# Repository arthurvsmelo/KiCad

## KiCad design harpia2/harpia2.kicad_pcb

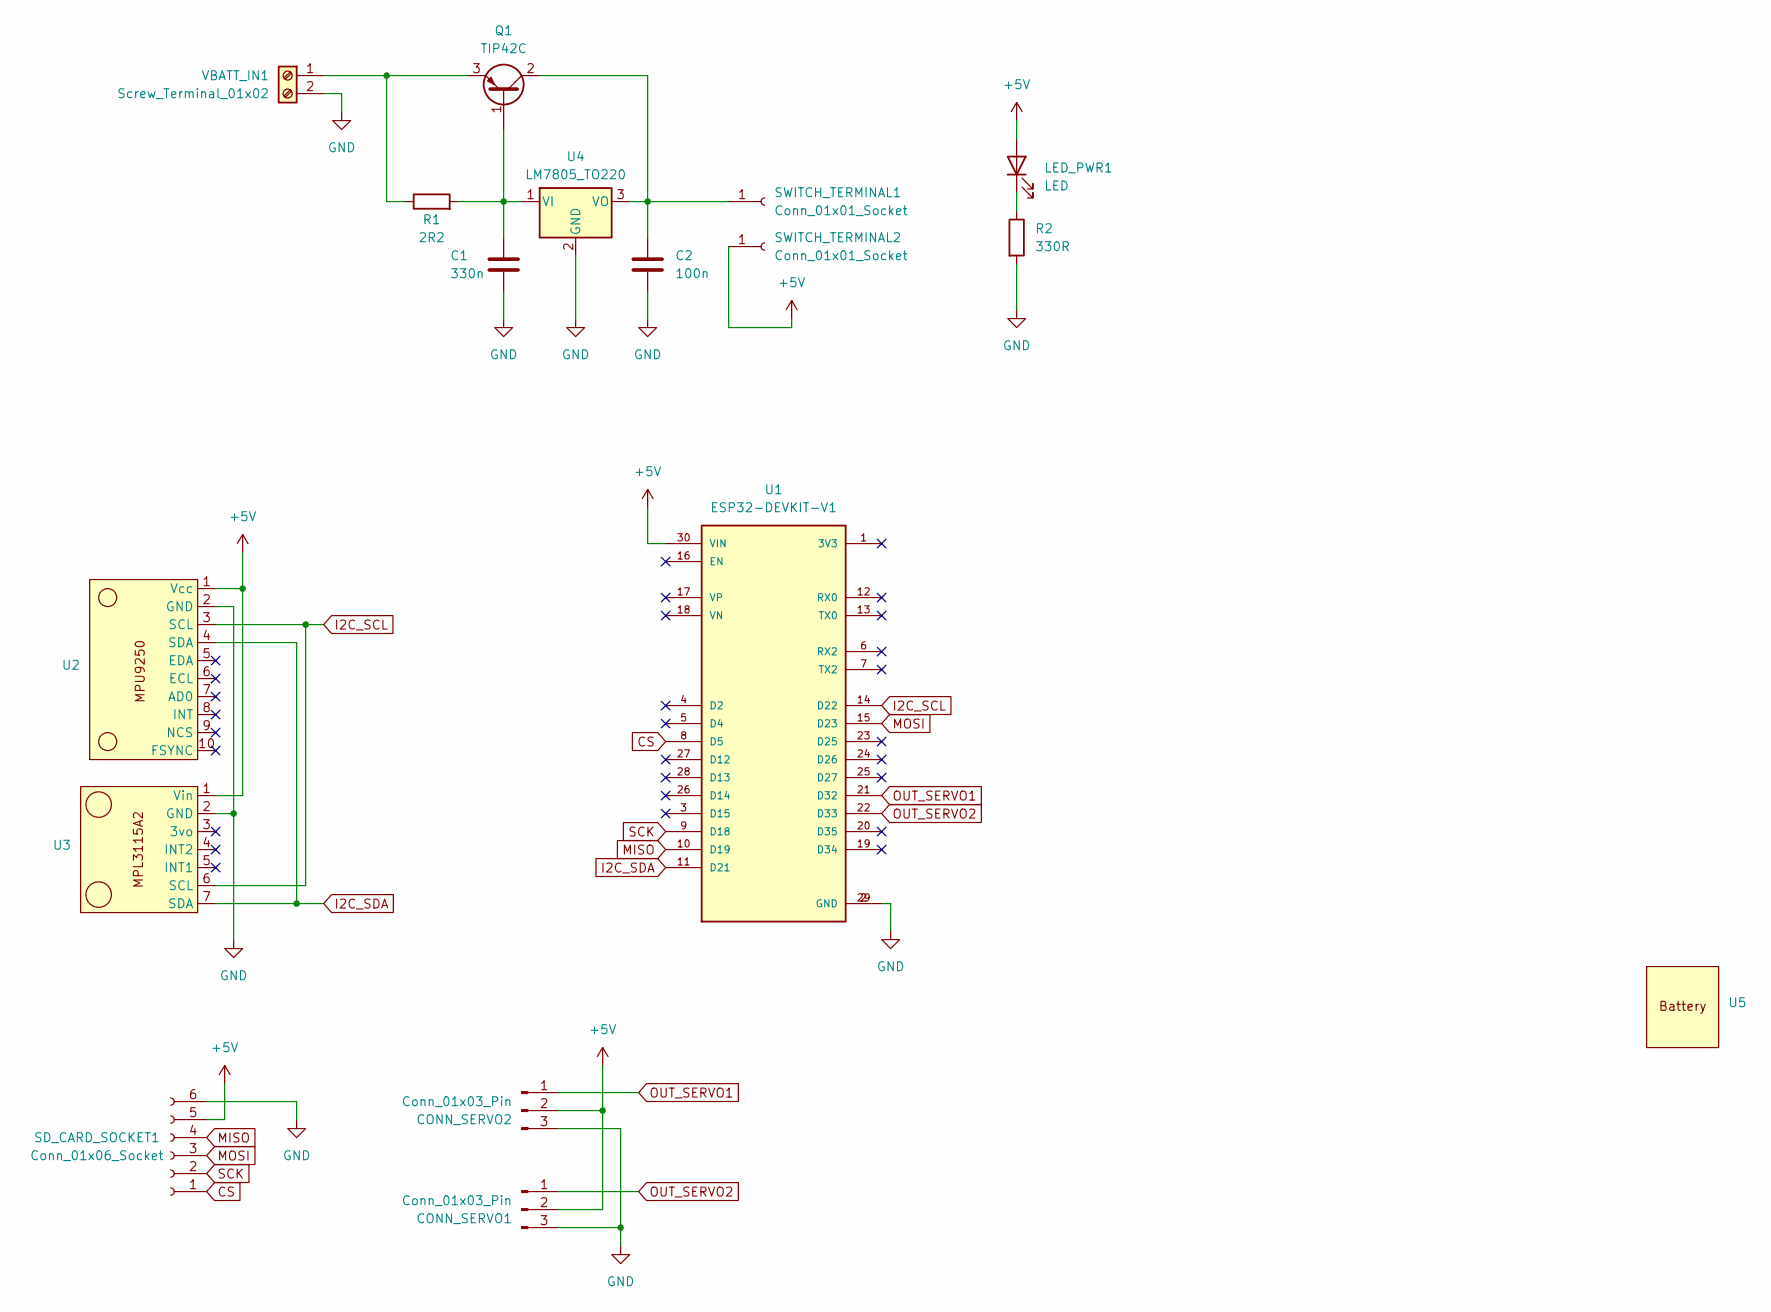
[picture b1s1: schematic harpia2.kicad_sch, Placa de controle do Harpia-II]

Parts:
C1: 330n; C_Rect_L9.0mm_W3.8mm_P7.50mm_MKT
C2: 100n; C_Rect_L9.0mm_W3.8mm_P7.50mm_MKT
CONN_SERVO1, CONN_SERVO2: Conn_01x03_Pin; PinHeader_1x03_P2.54mm_Vertical
LED_PWR1: LED; LED_D3.0mm_Clear
Q1: TIP42C; TO-220-3_Vertical
R1: 2R2; R_Axial_DIN0614_L14.3mm_D5.7mm_P20.32mm_Horizontal
R2: 330R; R_Axial_DIN0207_L6.3mm_D2.5mm_P15.24mm_Horizontal
SD_CARD_SOCKET1: Conn_01x06_Socket; PinSocket_1x06_P2.54mm_Vertical
SWITCH_TERMINAL1, SWITCH_TERMINAL2: Conn_01x01_Socket; PinSocket_1x01_P2.54mm_Vertical
U1: ESP32-DEVKIT-V1; MODULE_ESP32_DEVKIT_V1; PARTREV N/A
U2: MPU9250
U3: MPL3115A2
U4: LM7805_TO220; TO-220-3_Vertical
U5: 18650_BATTERY_HOLDER
VBATT_IN1: Screw_Terminal_01x02; TerminalBlock_Phoenix_MKDS-1,5-2-5.08_1x02_P5.08mm_Horizont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

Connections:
+5V: CONN_SERVO1.2, CONN_SERVO2.2, LED_PWR1.2 (A), SD_CARD_SOCKET1.5, SWITCH_TERMINAL2.1, U1.30 (VIN), U2.1 (Vcc), U3.1 (Vin)
CS: SD_CARD_SOCKET1.1, U1.8 (D5)
GND: C1.2, C2.2, CONN_SERVO1.3, CONN_SERVO2.3, R2.2, SD_CARD_SOCKET1.6, U1.2 (GND), U1.29 (GND), U2.2 (GND), U3.2 (GND), U4.2 (GND), VBATT_IN1.2
I2C_SCL: U1.14 (D22), U2.3 (SCL), U3.6 (SCL)
I2C_SDA: U1.11 (D21), U2.4 (SDA), U3.7 (SDA)
MISO: SD_CARD_SOCKET1.4, U1.10 (D19)
MOSI: SD_CARD_SOCKET1.3, U1.15 (D23)
unnamed: LED_PWR1.1 (K), R2.1
unnamed: C1.1, Q1.1 (B), R1.2, U4.1 (VI)
unnamed: C2.1, Q1.2 (C), SWITCH_TERMINAL1.1, U4.3 (VO)
unnamed: Q1.3 (E), R1.1, VBATT_IN1.1
OUT_SERVO1: CONN_SERVO2.1, U1.21 (D32)
OUT_SERVO2: CONN_SERVO1.1, U1.22 (D33)
SCK: SD_CARD_SOCKET1.2, U1.9 (D18)

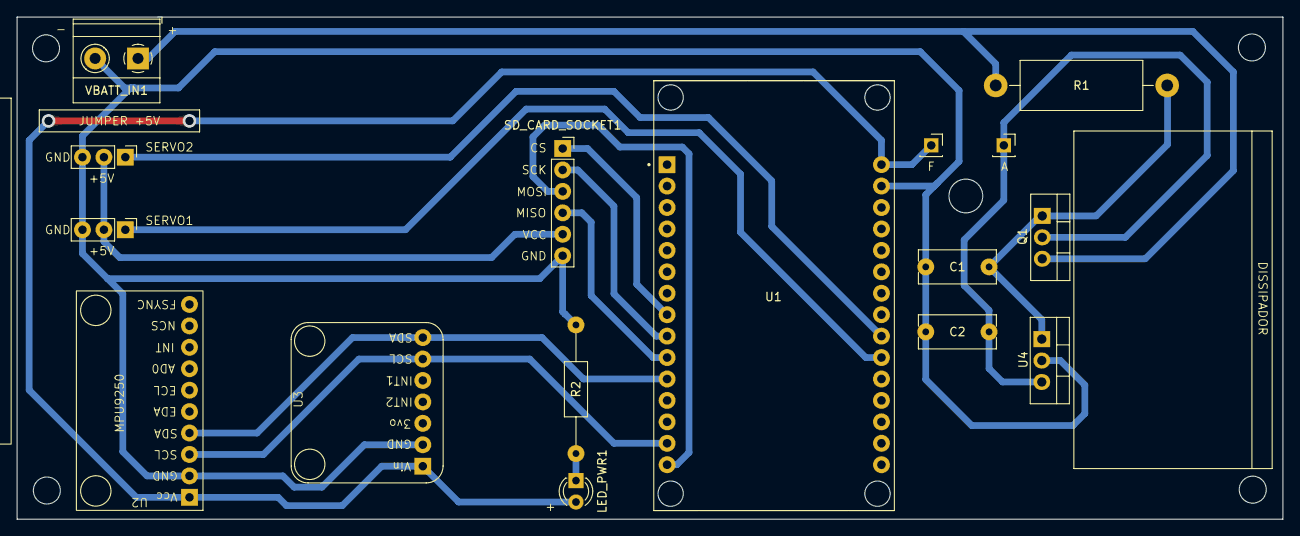
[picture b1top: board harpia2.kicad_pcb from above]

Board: 2 copper layers, 150.0 x 59.5 mm, 17 parts (0 on the bottom side), 14 nets.

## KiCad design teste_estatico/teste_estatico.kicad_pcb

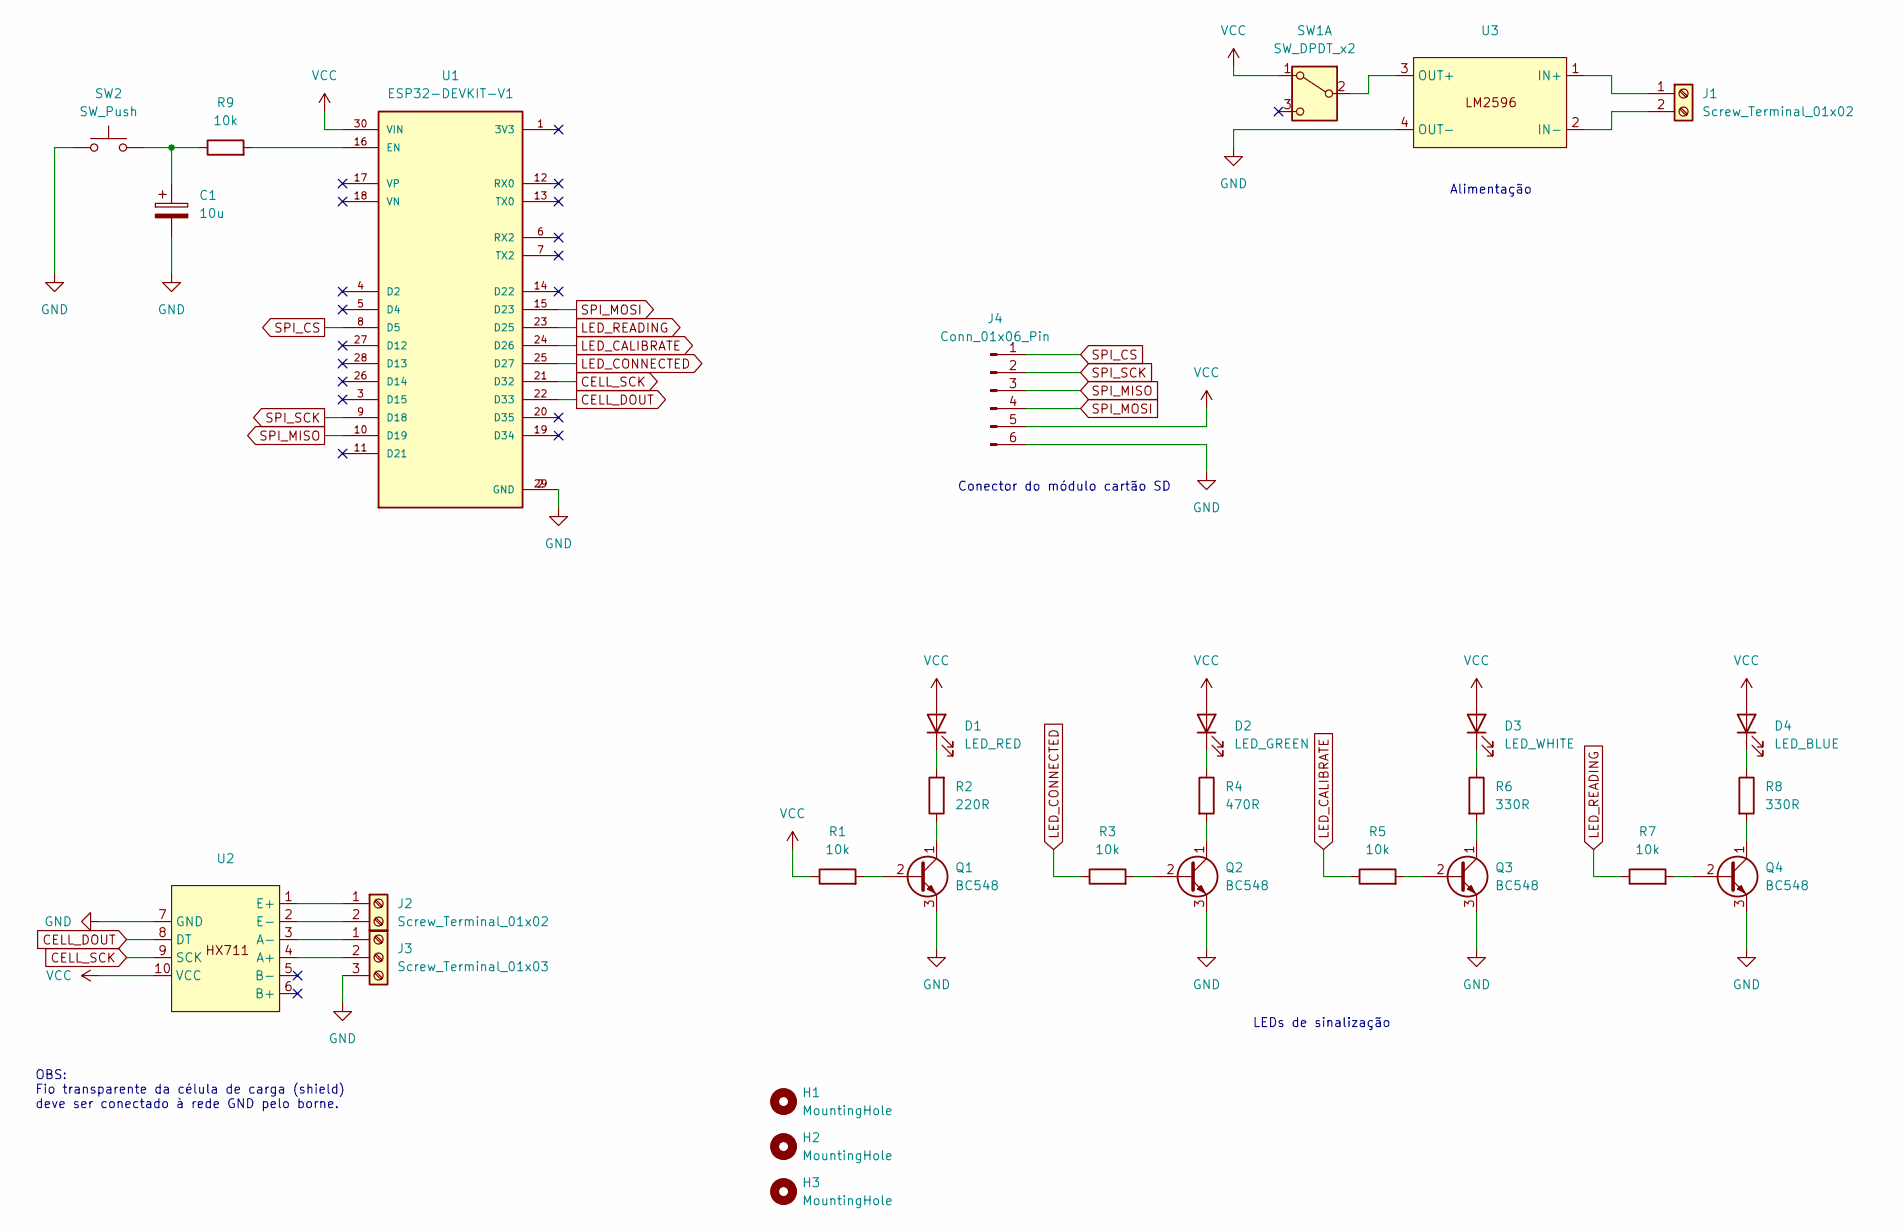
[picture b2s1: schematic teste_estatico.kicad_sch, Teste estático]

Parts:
C1: 10u; CP_Radial_D5.0mm_P2.50mm
D1: LED_RED; LED_D3.0mm_Horizontal_O1.27mm_Z2.0mm
D2: LED_GREEN; LED_D3.0mm_Horizontal_O1.27mm_Z2.0mm
D3: LED_WHITE; LED_D3.0mm_Horizontal_O1.27mm_Z2.0mm
D4: LED_BLUE; LED_D3.0mm_Horizontal_O1.27mm_Z2.0mm
H1, H2, H3: MountingHole; MountingHole_4.3mm_M4
J1, J2: Screw_Terminal_01x02; TerminalBlock_Phoenix_MKDS-1,5-2-5.08_1x02_P5.08mm_Horizont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
J3: Screw_Terminal_01x03; TerminalBlock_Phoenix_MKDS-1,5-3-5.08_1x03_P5.08mm_Horizont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
J4: Conn_01x06_Pin; PinSocket_1x06_P2.54mm_Vertical
Q1, Q2, Q3, Q4: BC548; TO-92_Wide
R1, R3, R5, R7, R9: 10k; R_Axial_DIN0207_L6.3mm_D2.5mm_P10.16mm_Horizontal
R2: 220R; R_Axial_DIN0207_L6.3mm_D2.5mm_P10.16mm_Horizontal
R4: 470R; R_Axial_DIN0207_L6.3mm_D2.5mm_P10.16mm_Horizontal
R6, R8: 330R; R_Axial_DIN0207_L6.3mm_D2.5mm_P10.16mm_Horizontal
SW1: SW_DPDT_x2; push_button_DPDT_6pin
SW2: SW_Push; SW_Tactile_SPST_Angled_PTS645Vx39-2LFS
U1: ESP32-DEVKIT-V1; MODULE_ESP32_DEVKIT_V1; PARTREV N/A
U2: HX711_module
U3: LM2596_module

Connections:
CELL_DOUT: U1.22 (D33), U2.8 (DT)
CELL_SCK: U1.21 (D32), U2.9 (SCK)
GND: C1.2, J3.3, J4.6, Q1.3 (E), Q2.3 (E), Q3.3 (E), Q4.3 (E), SW2.1, U1.2 (GND), U1.29 (GND), U2.7 (GND), U3.4 (OUT-)
LED_CALIBRATE: R5.1, U1.24 (D26)
LED_CONNECTED: R3.1, U1.25 (D27)
LED_READING: R7.1, U1.23 (D25)
unnamed: C1.1, R9.1, SW2.2
unnamed: D1.1 (K), R2.2
unnamed: D2.1 (K), R4.1
unnamed: D3.1 (K), R6.1
unnamed: D4.1 (K), R8.1
unnamed: J1.1, U3.1 (IN+)
unnamed: J1.2, U3.2 (IN-)
unnamed: J2.1, U2.1 (E+)
unnamed: J2.2, U2.2 (E-)
unnamed: J3.1, U2.3 (A-)
unnamed: J3.2, U2.4 (A+)
unnamed: Q1.2 (B), R1.2
unnamed: Q1.1 (C), R2.1
unnamed: Q2.2 (B), R3.2
unnamed: Q2.1 (C), R4.2
unnamed: Q3.2 (B), R5.2
unnamed: Q3.1 (C), R6.2
unnamed: Q4.2 (B), R7.2
unnamed: Q4.1 (C), R8.2
unnamed: SW1.2 (B), U3.3 (OUT+)
unnamed: R9.2, U1.16 (EN)
SPI_CS: J4.1, U1.8 (D5)
SPI_MISO: J4.3, U1.10 (D19)
SPI_MOSI: J4.4, U1.15 (D23)
SPI_SCK: J4.2, U1.9 (D18)
VCC: D1.2 (A), D2.2 (A), D3.2 (A), D4.2 (A), J4.5, R1.1, SW1.1 (A), U1.30 (VIN), U2.10 (VCC)

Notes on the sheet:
Alimentação
LEDs de sinalização
Conector do módulo cartão SD
OBS: Fio transparente da célula de carga (shield) deve ser conectado à rede GND pelo borne.

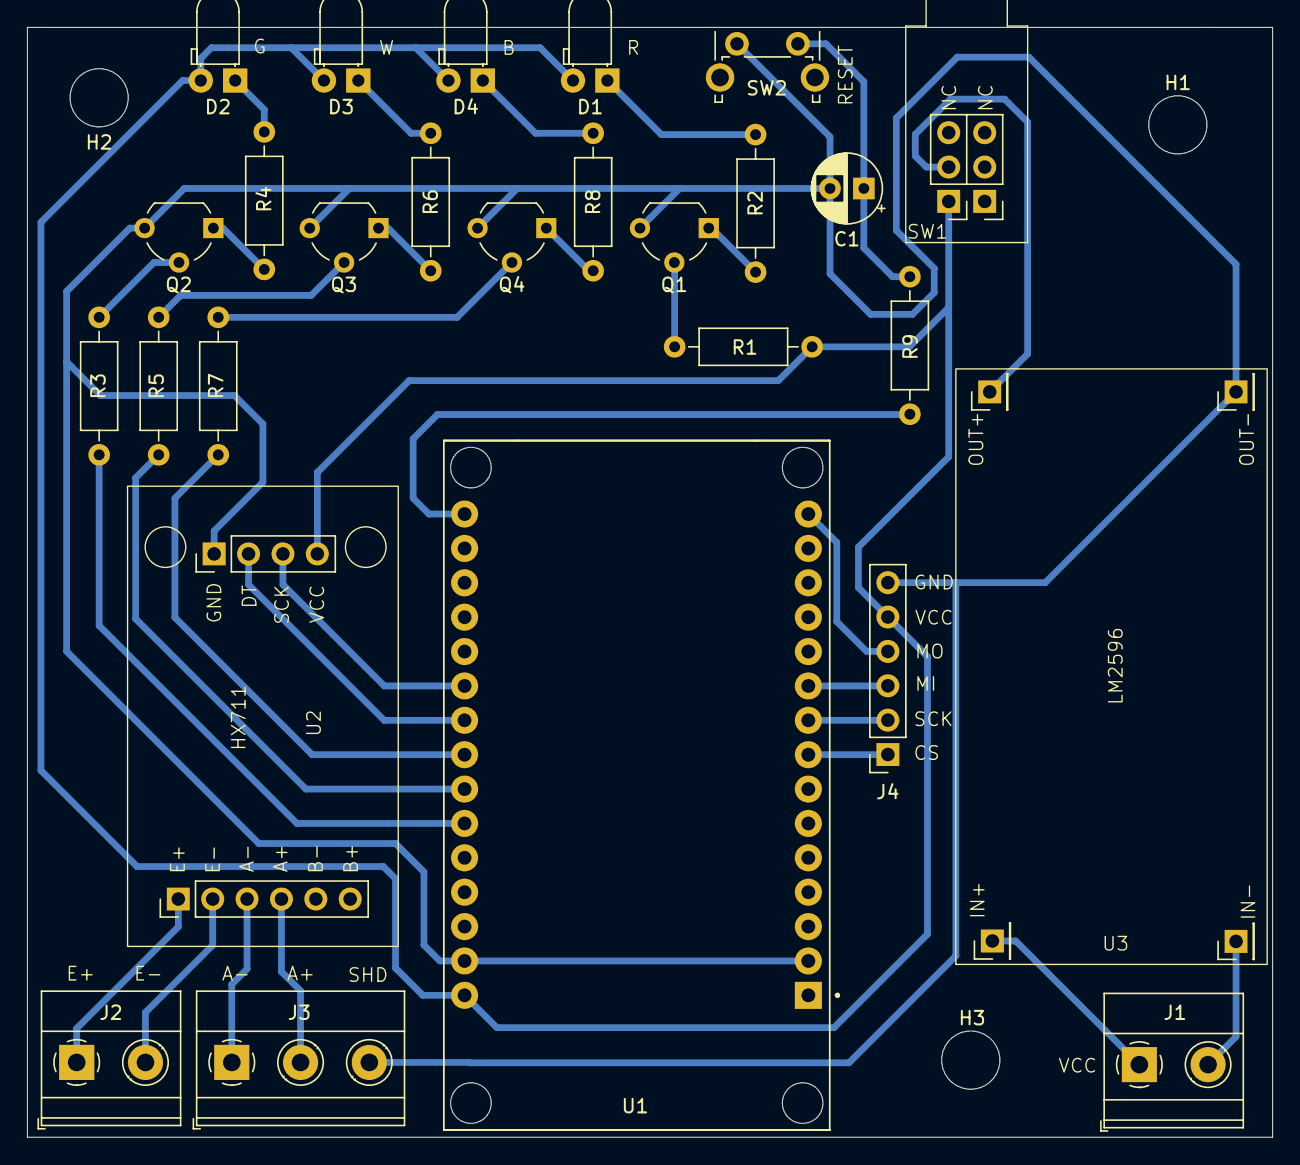
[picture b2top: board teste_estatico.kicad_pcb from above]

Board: 2 copper layers, 92.0 x 82.0 mm, 30 parts (0 on the bottom side), 32 nets.

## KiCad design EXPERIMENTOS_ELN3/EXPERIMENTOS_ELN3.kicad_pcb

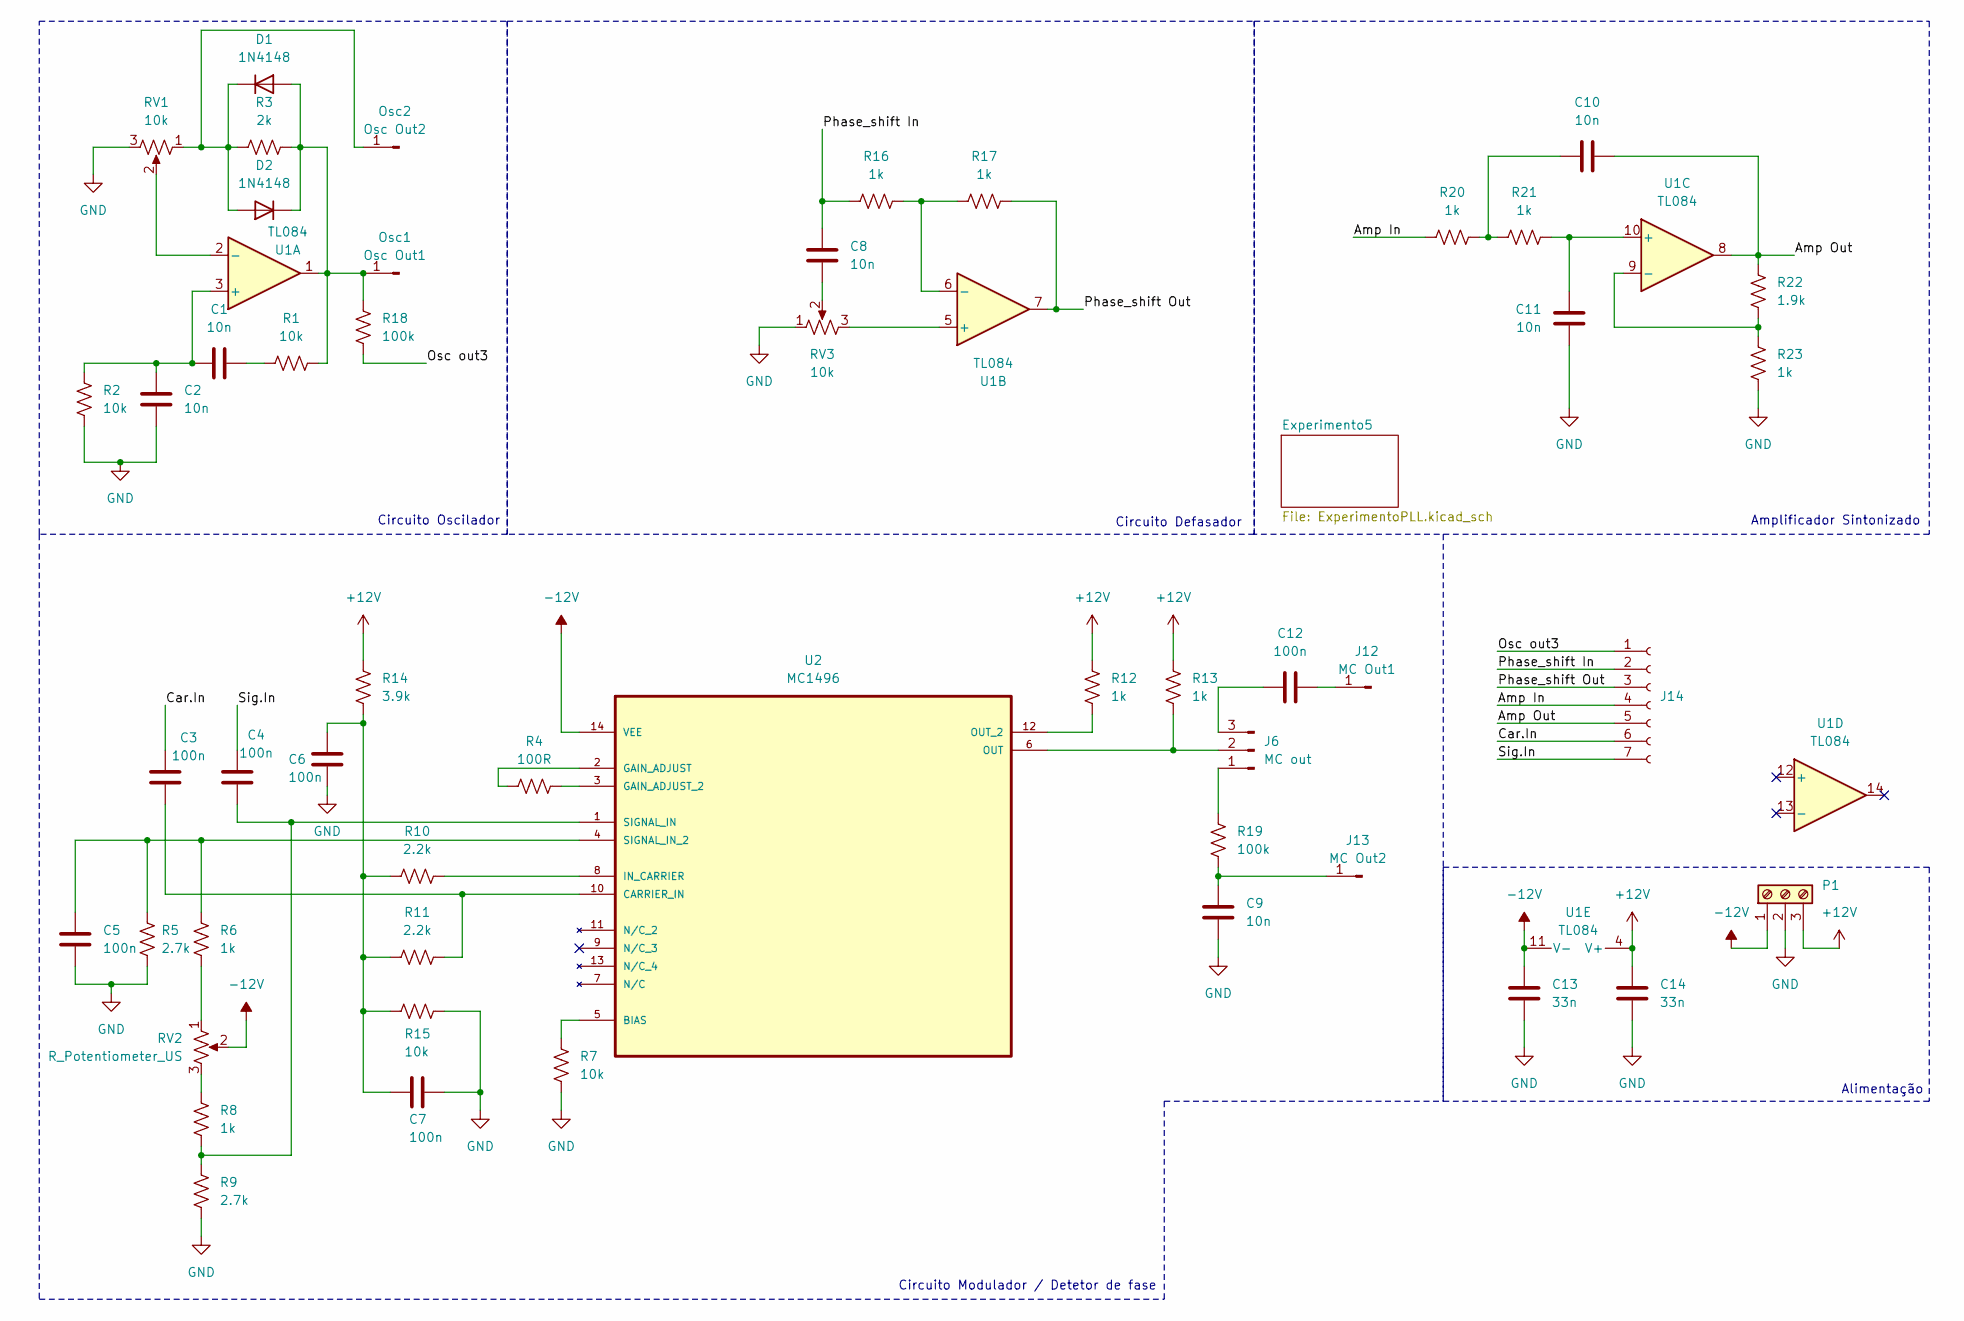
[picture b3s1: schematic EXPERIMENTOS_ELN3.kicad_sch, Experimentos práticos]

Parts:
C1, C2, C8, C9, C10, C11: 10n; C_Rect_L10.0mm_W4.0mm_P7.50mm_MKS4
C3, C4, C5, C6, C7, C12: 100n; C_Rect_L10.0mm_W4.0mm_P7.50mm_MKS4
C13, C14: 33n; C_Rect_L10.0mm_W4.0mm_P7.50mm_MKS4
D1, D2: 1N4148; D_DO-35_SOD27_P7.62mm_Horizontal
J6: MC out; PinHeader_1x03_P2.54mm_Vertical
J12: MC Out1; PinHeader_1x01_P2.54mm_Vertical
J13: MC Out2; PinHeader_1x01_P2.54mm_Vertical
J14: Conn_01x07_Socket; PinSocket_1x07_P2.54mm_Vertical
Osc1: Osc Out1; PinHeader_1x01_P2.54mm_Vertical
Osc2: Osc Out2; PinHeader_1x01_P2.54mm_Vertical
P1: Screw_Terminal_01x03; TerminalBlock_Phoenix_MKDS-1,5-3-5.08_1x03_P5.08mm_Horizont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
R1, R2, R7, R15: 10k; R_Axial_DIN0207_L6.3mm_D2.5mm_P10.16mm_Horizontal
R3: 2k; R_Axial_DIN0207_L6.3mm_D2.5mm_P10.16mm_Horizontal
R4: 100R; R_Axial_DIN0207_L6.3mm_D2.5mm_P10.16mm_Horizontal
R5, R9: 2.7k; R_Axial_DIN0207_L6.3mm_D2.5mm_P10.16mm_Horizontal
R6, R8, R12, R13, R16, R17, R20, R21, R23: 1k; R_Axial_DIN0207_L6.3mm_D2.5mm_P10.16mm_Horizontal
R10, R11: 2.2k; R_Axial_DIN0207_L6.3mm_D2.5mm_P10.16mm_Horizontal
R14: 3.9k; R_Axial_DIN0207_L6.3mm_D2.5mm_P10.16mm_Horizontal
R18, R19: 100k; R_Axial_DIN0207_L6.3mm_D2.5mm_P10.16mm_Horizontal
R22: 1.9k; R_Axial_DIN0207_L6.3mm_D2.5mm_P10.16mm_Horizontal
RV1, RV3: 10k; Potentiometer_Bourns_3296W_Vertical
RV2: R_Potentiometer_US; Potentiometer_Bourns_3296W_Vertical
U1: TL084; MC1496BPG
U2: MC1496; CERDIP-14_W7.62mm_SideBrazed_LongPads; MPN MC1496BPG

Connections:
+12V: C14.2, P1.3, R12.1, R13.1, R14.1, U1.4 (V+)
-12V: C13.2, P1.1, RV2.2, U1.11 (V-), U2.14 (VEE)
/Amp In: J14.4, R20.1
/Amp Out: C10.2, J14.5, R22.2, U1.8
/Car.In: C3.1, J14.6
/Osc out3: J14.1, R18.1
/Phase_shift In: C8.1, J14.2, R16.1
/Phase_shift Out: J14.3, R17.2, U1.7
/Sig.In: C4.1, J14.7
GND: C2.2, C5.2, C6.1, C7.1, C9.2, C11.2, C13.1, C14.1, P1.2, R2.2, R5.1, R7.2, R9.2, R15.1, R23.1, RV1.3, RV3.1; also elsewhere on the board
unnamed: C1.2, R1.1
unnamed: C6.2, C7.2, R10.1, R11.1, R14.2, R15.2
unnamed: C8.2, RV3.2
unnamed: C10.1, R20.2, R21.1
unnamed: D1.2 (A), D2.1 (K), Osc1.1, R1.2, R3.2, R18.2, U1.1
unnamed: D1.1 (K), D2.2 (A), Osc2.1, R3.1, RV1.1
unnamed: J6.1, R19.2
unnamed: J6.2, R13.2, U2.6 (OUT)
unnamed: C12.1, J6.3
unnamed: C12.2, J12.1
unnamed: C9.1, J13.1, R19.1
unnamed: R6.1, RV2.1
unnamed: R8.1, RV2.3
unnamed: C1.1, C2.1, R2.1, U1.3 (+)
unnamed: RV1.2, U1.2 (-)
unnamed: RV3.3, U1.5 (+)
unnamed: R16.2, R17.1, U1.6 (-)
unnamed: C11.1, R21.2, U1.10 (+)
unnamed: R22.1, R23.2, U1.9 (-)
unnamed: R7.1, U2.5 (BIAS)
unnamed: C3.2, R11.2, U2.10 (CARRIER_IN)
unnamed: R4.1, U2.2 (GAIN_ADJUST)
unnamed: R4.2, U2.3 (GAIN_ADJUST_2)
unnamed: R10.2, U2.8 (IN_CARRIER)
unnamed: R12.2, U2.12 (OUT_2)
unnamed: C4.2, R8.2, R9.1, U2.1 (SIGNAL_IN)
unnamed: C5.1, R5.2, R6.2, U2.4 (SIGNAL_IN_2)

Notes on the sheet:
Amplificador Sintonizado
Alimentação
Circuito Modulador / Detetor de fase
Circuito Defasador
Circuito Oscilador

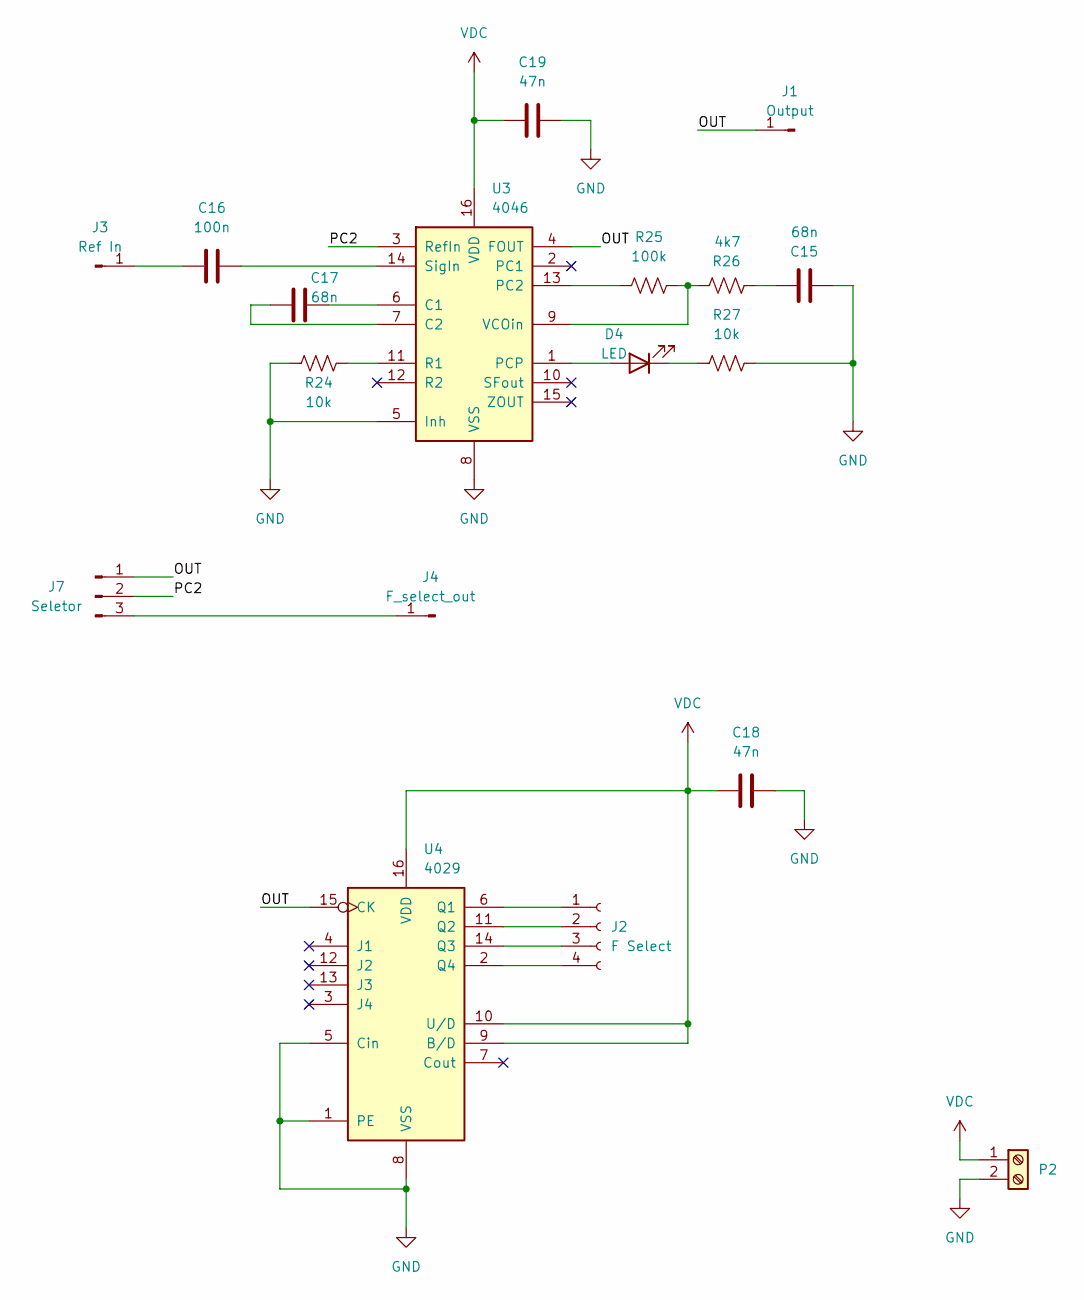
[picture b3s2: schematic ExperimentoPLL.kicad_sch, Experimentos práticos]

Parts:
C15: 68n; C_Disc_D3.8mm_W2.6mm_P2.50mm
C16: 100n; C_Rect_L9.0mm_W2.5mm_P7.50mm_MKT
C17: 68n; C_Disc_D3.4mm_W2.1mm_P2.50mm
C18, C19: 47n; C_Disc_D3.4mm_W2.1mm_P2.50mm
D4: LED; LED_D3.0mm
J1: Output; PinHeader_1x01_P2.54mm_Vertical
J2: F Select; PinSocket_1x04_P2.54mm_Vertical
J3: Ref In; PinHeader_1x01_P2.54mm_Vertical
J4: F_select_out; PinHeader_1x01_P2.54mm_Vertical
J7: Seletor; PinHeader_1x03_P2.54mm_Vertical
P2: Screw_Terminal_01x02; TerminalBlock_Phoenix_MKDS-1,5-2-5.08_1x02_P5.08mm_Horizont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
R24, R27: 10k; R_Axial_DIN0207_L6.3mm_D2.5mm_P10.16mm_Horizontal
R25: 100k; R_Axial_DIN0207_L6.3mm_D2.5mm_P10.16mm_Horizontal
R26: 4k7; R_Axial_DIN0207_L6.3mm_D2.5mm_P10.16mm_Horizontal
U3: 4046; DIP-16_W7.62mm_LongPads
U4: 4029; DIP-16_W7.62mm_LongPads

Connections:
/Experimento5/OUT: J1.1, J7.1, U3.4 (FOUT), U4.15 (CK)
/Experimento5/PC2: J7.2, U3.3 (RefIn)
GND: C15.2, C18.2, C19.2, P2.2, R24.1, R27.2, U3.5 (Inh), U3.8 (VSS), U4.1 (PE), U4.5 (Cin), U4.8 (VSS); also elsewhere on the board
unnamed: C15.1, R26.2
unnamed: D4.2 (A), U3.1 (PCP)
unnamed: D4.1 (K), R27.1
unnamed: J2.1, U4.6 (Q1)
unnamed: J2.2, U4.11 (Q2)
unnamed: J2.3, U4.14 (Q3)
unnamed: J2.4, U4.2 (Q4)
unnamed: C16.1, J3.1
unnamed: J4.1, J7.3
unnamed: C17.2, U3.6 (C1)
unnamed: C17.1, U3.7 (C2)
unnamed: R25.1, U3.13 (PC2)
unnamed: R24.2, U3.11 (R1)
unnamed: C16.2, U3.14 (SigIn)
unnamed: R25.2, R26.1, U3.9 (VCOin)
VDC: C18.1, C19.1, P2.1, U3.16 (VDD), U4.9 (B/D), U4.10 (U/D), U4.16 (VDD)

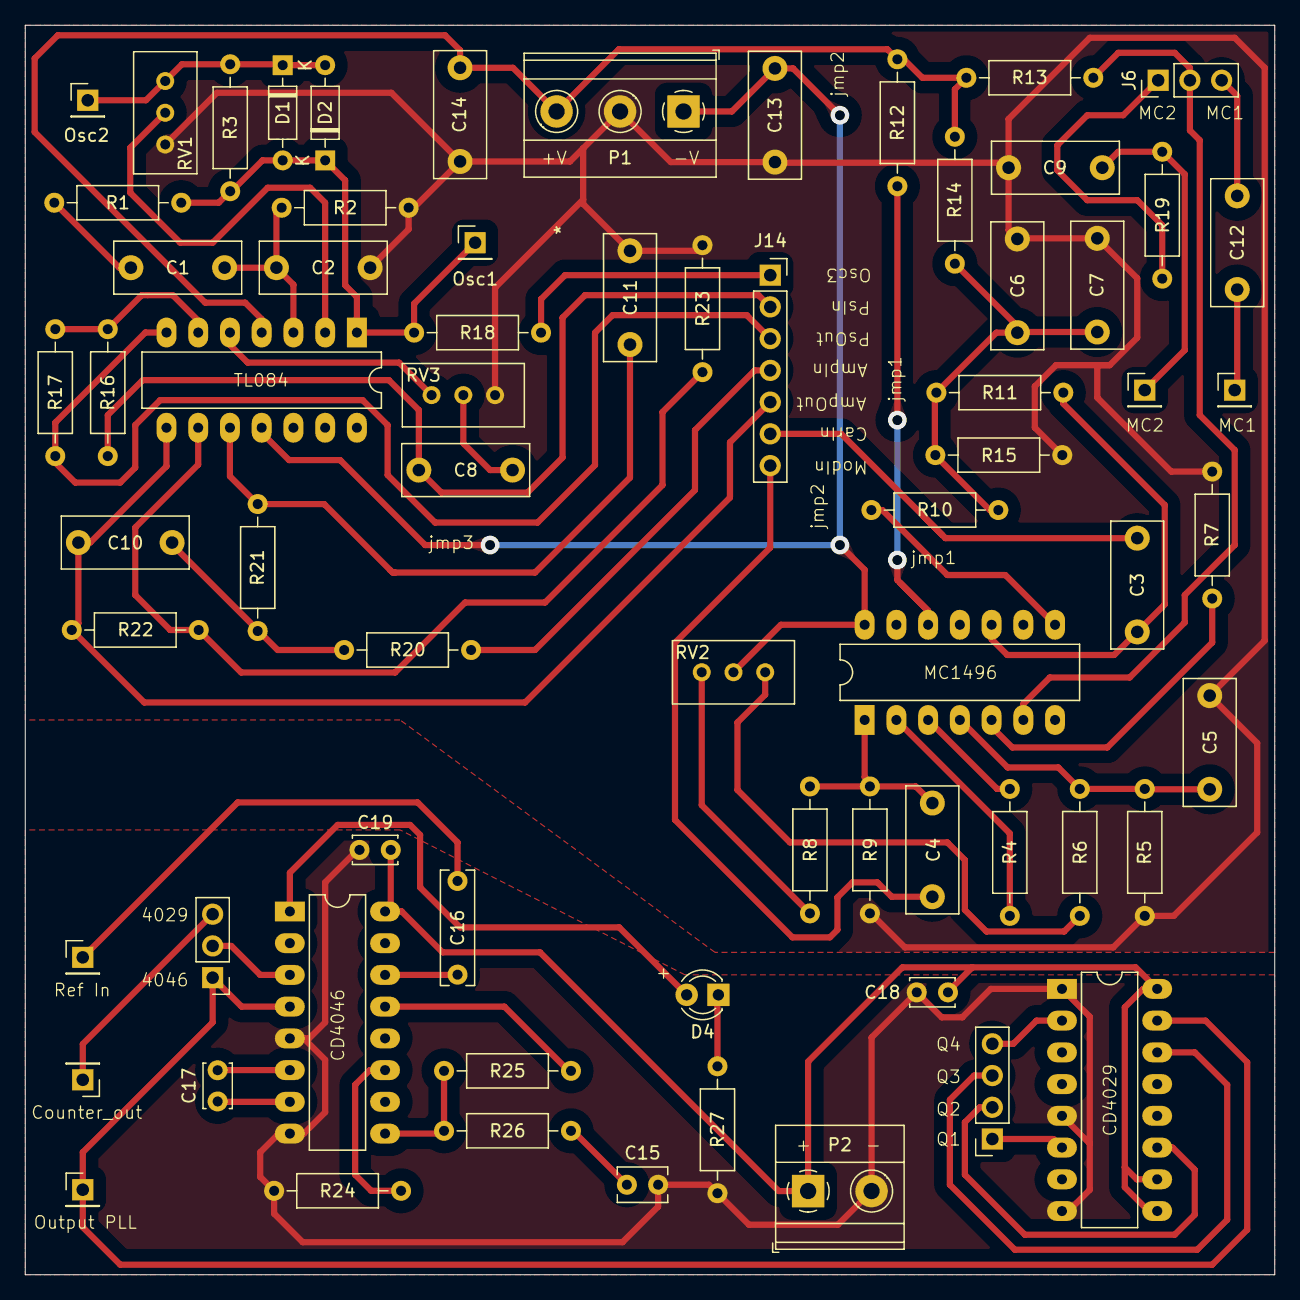
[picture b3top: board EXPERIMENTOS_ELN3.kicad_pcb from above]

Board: 2 copper layers, 100.0 x 100.0 mm, 69 parts (0 on the bottom side), 55 nets.

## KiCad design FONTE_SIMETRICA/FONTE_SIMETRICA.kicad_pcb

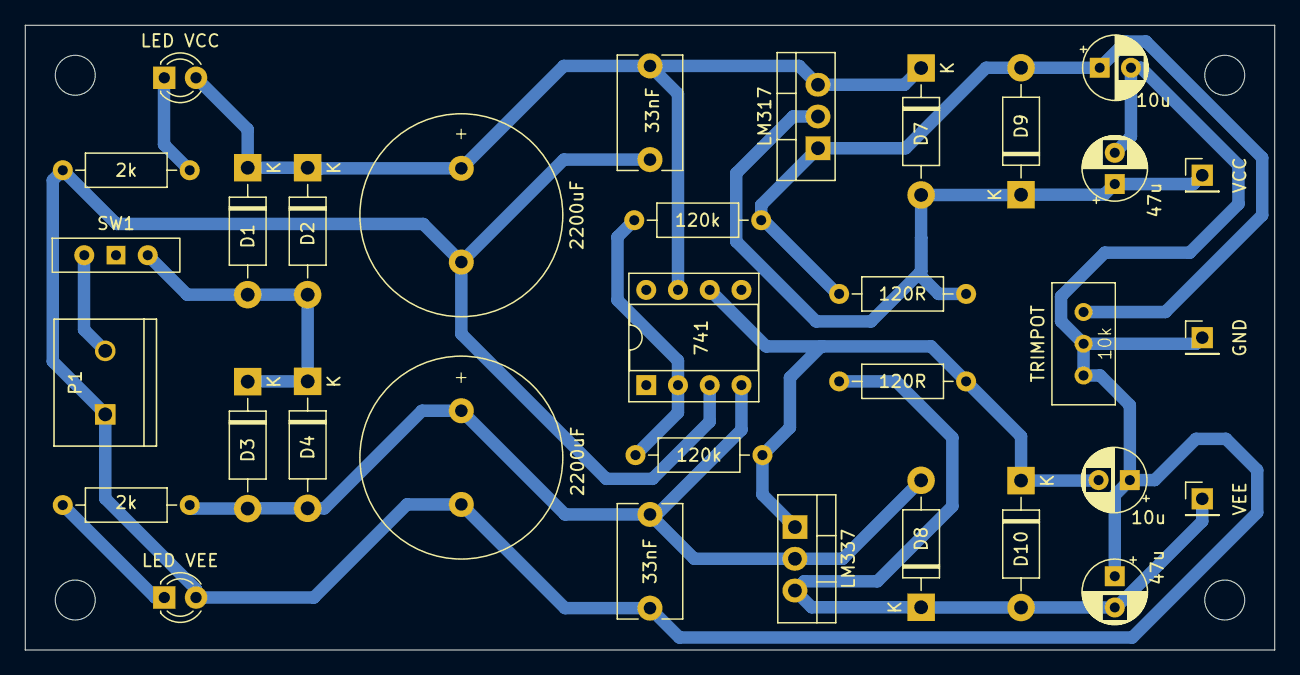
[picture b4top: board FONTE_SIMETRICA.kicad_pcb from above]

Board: 2 copper layers, 100.0 x 50.0 mm, 37 parts (0 on the bottom side), 12 nets.

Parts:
2k, 2k#2: 2k; R_Axial_DIN0207_L6.3mm_D2.5mm_P10.16mm_Horizontal
10u, 10u#2: 10u; CP_Radial_D5.0mm_P2.50mm
33nF, 33nF#2: 33n; C_Disc_D9.0mm_W5.0mm_P7.50mm
47u, 47u#2: 47u; CP_Radial_D5.0mm_P2.50mm
120R, 120R#2: 120R; R_Axial_DIN0207_L6.3mm_D2.5mm_P10.16mm_Horizontal
120k, 120k#2: 120k; R_Axial_DIN0207_L6.3mm_D2.5mm_P10.16mm_Horizontal
741: LM741; DIP-8_W7.62mm_Socket
2200uF, 2200uF#2: 2200u; C_Radial_D16.0mm_H25.0mm_P7.50mm
D1, D2, D3, D4, D7, D8, D9, D10: 1N4007; D_DO-41_SOD81_P10.16mm_Horizontal
GND: Conn_01x01_Pin; PinHeader_1x01_P2.54mm_Vertical
H1, H2, H3, H4: MountingHole; MountingHole_3.2mm_M3
LED VCC: LED; LED_D3.0mm
LED VEE: LED; LED_D3.0mm
LM317: LM317_TO-220; TO-220-3_Vertical
LM337: LM337_TO220; TO-220-3_Vertical
P1: BORNE_KRE
SW1: SW_SPDT; SW_Slide-03_Wuerth-WS-SLTV_10x2.5x6.4_P2.54mm
TRIMPOT: 5k; Potentiometer_Bourns_3296W_Vertical
VCC: Conn_01x01_Pin; PinHeader_1x01_P2.54mm_Vertical
VEE: Conn_01x01_Pin; PinHeader_1x01_P2.54mm_Vertical

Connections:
/GND: 2k.2, 10u.2, 10u#2.1, 33nF.2, 33nF#2.1, 47u.1, 47u#2.2, 741.3 (+), 2200uF.2, 2200uF#2.1, GND.1, LED VEE.2 (A), P1.1, TRIMPOT.2, TRIMPOT.3
/VCC: 33nF.1, 741.7 (V+), 2200uF.1, D1.1 (K), D2.1 (K), D7.1 (K), LED VCC.2 (A), LM317.3 (VI)
/VEE: 2k#2.2, 33nF#2.2, 741.4 (V-), 2200uF#2.2, D3.2 (A), D4.2 (A), D8.2 (A), LM337.2 (VI)
unnamed: D1.2 (A), D2.2 (A), D3.1 (K), D4.1 (K), SW1.3 (C)
unnamed: 2k.1, LED VCC.1 (K)
unnamed: 2k#2.1, LED VEE.1 (K)
unnamed: 47u#2.1, 120R#2.1, D7.2 (A), D9.1 (K), LM317.2 (VO), VCC.1
unnamed: 10u.1, 120R#2.2, 120k.1, D9.2 (A), LM317.1 (ADJ), TRIMPOT.1
unnamed: 47u.2, 120R.2, D8.1 (K), D10.2 (A), LM337.3 (VO), VEE.1
unnamed: 10u#2.2, 120R.1, 120k#2.2, 741.6, D10.1 (K), LM337.1 (ADJ)
unnamed: P1.2, SW1.2 (B)
unnamed: 120k.2, 120k#2.1, 741.2 (-)

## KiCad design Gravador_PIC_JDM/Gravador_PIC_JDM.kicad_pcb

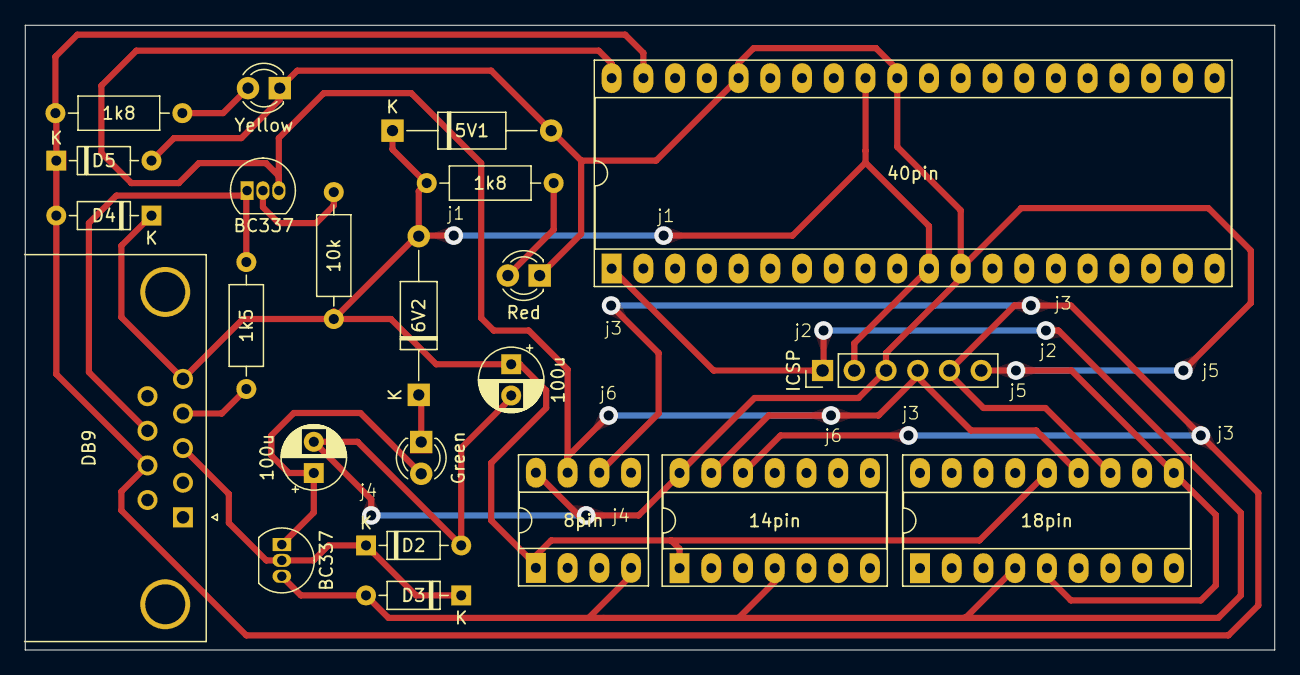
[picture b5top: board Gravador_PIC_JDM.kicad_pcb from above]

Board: 2 copper layers, 100.0 x 50.0 mm, 23 parts (0 on the bottom side), 13 nets.

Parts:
1k5, 1k8, 1k8#2, 10k: R_US; R_Axial_DIN0207_L6.3mm_D2.5mm_P10.16mm_Horizontal
5V1, 6V2: D_Zener; D_A-405_P12.70mm_Horizontal
8pin: Conn_02x04_Counter_Clockwise; DIP-8_W7.62mm_Socket_LongPads
14pin: Conn_02x07_Counter_Clockwise; DIP-14_W7.62mm_Socket_LongPads
18pin: Conn_02x09_Counter_Clockwise; DIP-18_W7.62mm_Socket_LongPads
40pin: Conn_02x20_Counter_Clockwise; DIP-40_W15.24mm_Socket_LongPads
100u, 100u#2: C_Polarized; CP_Radial_D5.0mm_P2.50mm
BC337, BC337#2: BC337; TO-92_Inline
D2, D3, D4, D5: 1N4148; D_DO-35_SOD27_P7.62mm_Horizontal
DB9: DE9_Receptacle_MountingHoles; DSUB-9_Female_Horizontal_P2.77x2.84mm_EdgePinOffset9.90mm_H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
Green: LED; LED_D3.0mm
ICSP: Conn_01x06; PinHeader_1x06_P2.54mm_Vertical
Red: LED; LED_D3.0mm
Yellow: LED; LED_D3.0mm

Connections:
/GND/PGM: 5V1.2 (A), 8pin.8, 14pin.14, 18pin.5, 18pin.10, 40pin.12, 40pin.31, 40pin.36, 100u.2, 100u#2.2, D2.2 (A), D5.2 (A), ICSP.3, ICSP.6, Red.1 (K), Yellow.1 (K)
/MCLR: 8pin.4, 14pin.4, 18pin.4, 40pin.1, BC337.3 (E), D3.2 (A), ICSP.1
/PGC: 1k8#2.1, 8pin.6, 14pin.12, 18pin.12, 40pin.39, D4.2 (A), D5.1 (K), DB9.7, ICSP.5
/PGD: 8pin.7, 14pin.13, 18pin.13, 40pin.40, BC337#2.3 (E), ICSP.4
/VDD: 1k8.1, 5V1.1 (K), 6V2.2 (A), 8pin.1, 10k.2, 14pin.1, 18pin.14, 40pin.11, 40pin.32, 100u.1, D4.1 (K), DB9.5, ICSP.2
unnamed: 1k5.1, DB9.4
unnamed: 6V2.1 (K), Green.1 (K)
unnamed: BC337.2 (B), D2.1 (K), D3.1 (K), DB9.3
unnamed: 100u#2.1, BC337.1 (C), Green.2 (A)
unnamed: 10k.1, BC337#2.2 (B)
unnamed: 1k5.2, BC337#2.1 (C), DB9.8
unnamed: 1k8.2, Red.2 (A)
unnamed: 1k8#2.2, Yellow.2 (A)
